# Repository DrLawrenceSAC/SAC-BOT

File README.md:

# SAC-BOT
A repository for the design and development of low-cost, open-source, beginner robotics platforms tailored to competition in RoboCup Junior events.

The design goals for these designs are as follows:
- low-cost for ease of addoption within and beyond our program
- functional, not perfect - allowing immediate engagement, and encouraing student-led modification and improvement.
- designed for specific goals of [RoboCup Junior](https://www.robocup.org/)

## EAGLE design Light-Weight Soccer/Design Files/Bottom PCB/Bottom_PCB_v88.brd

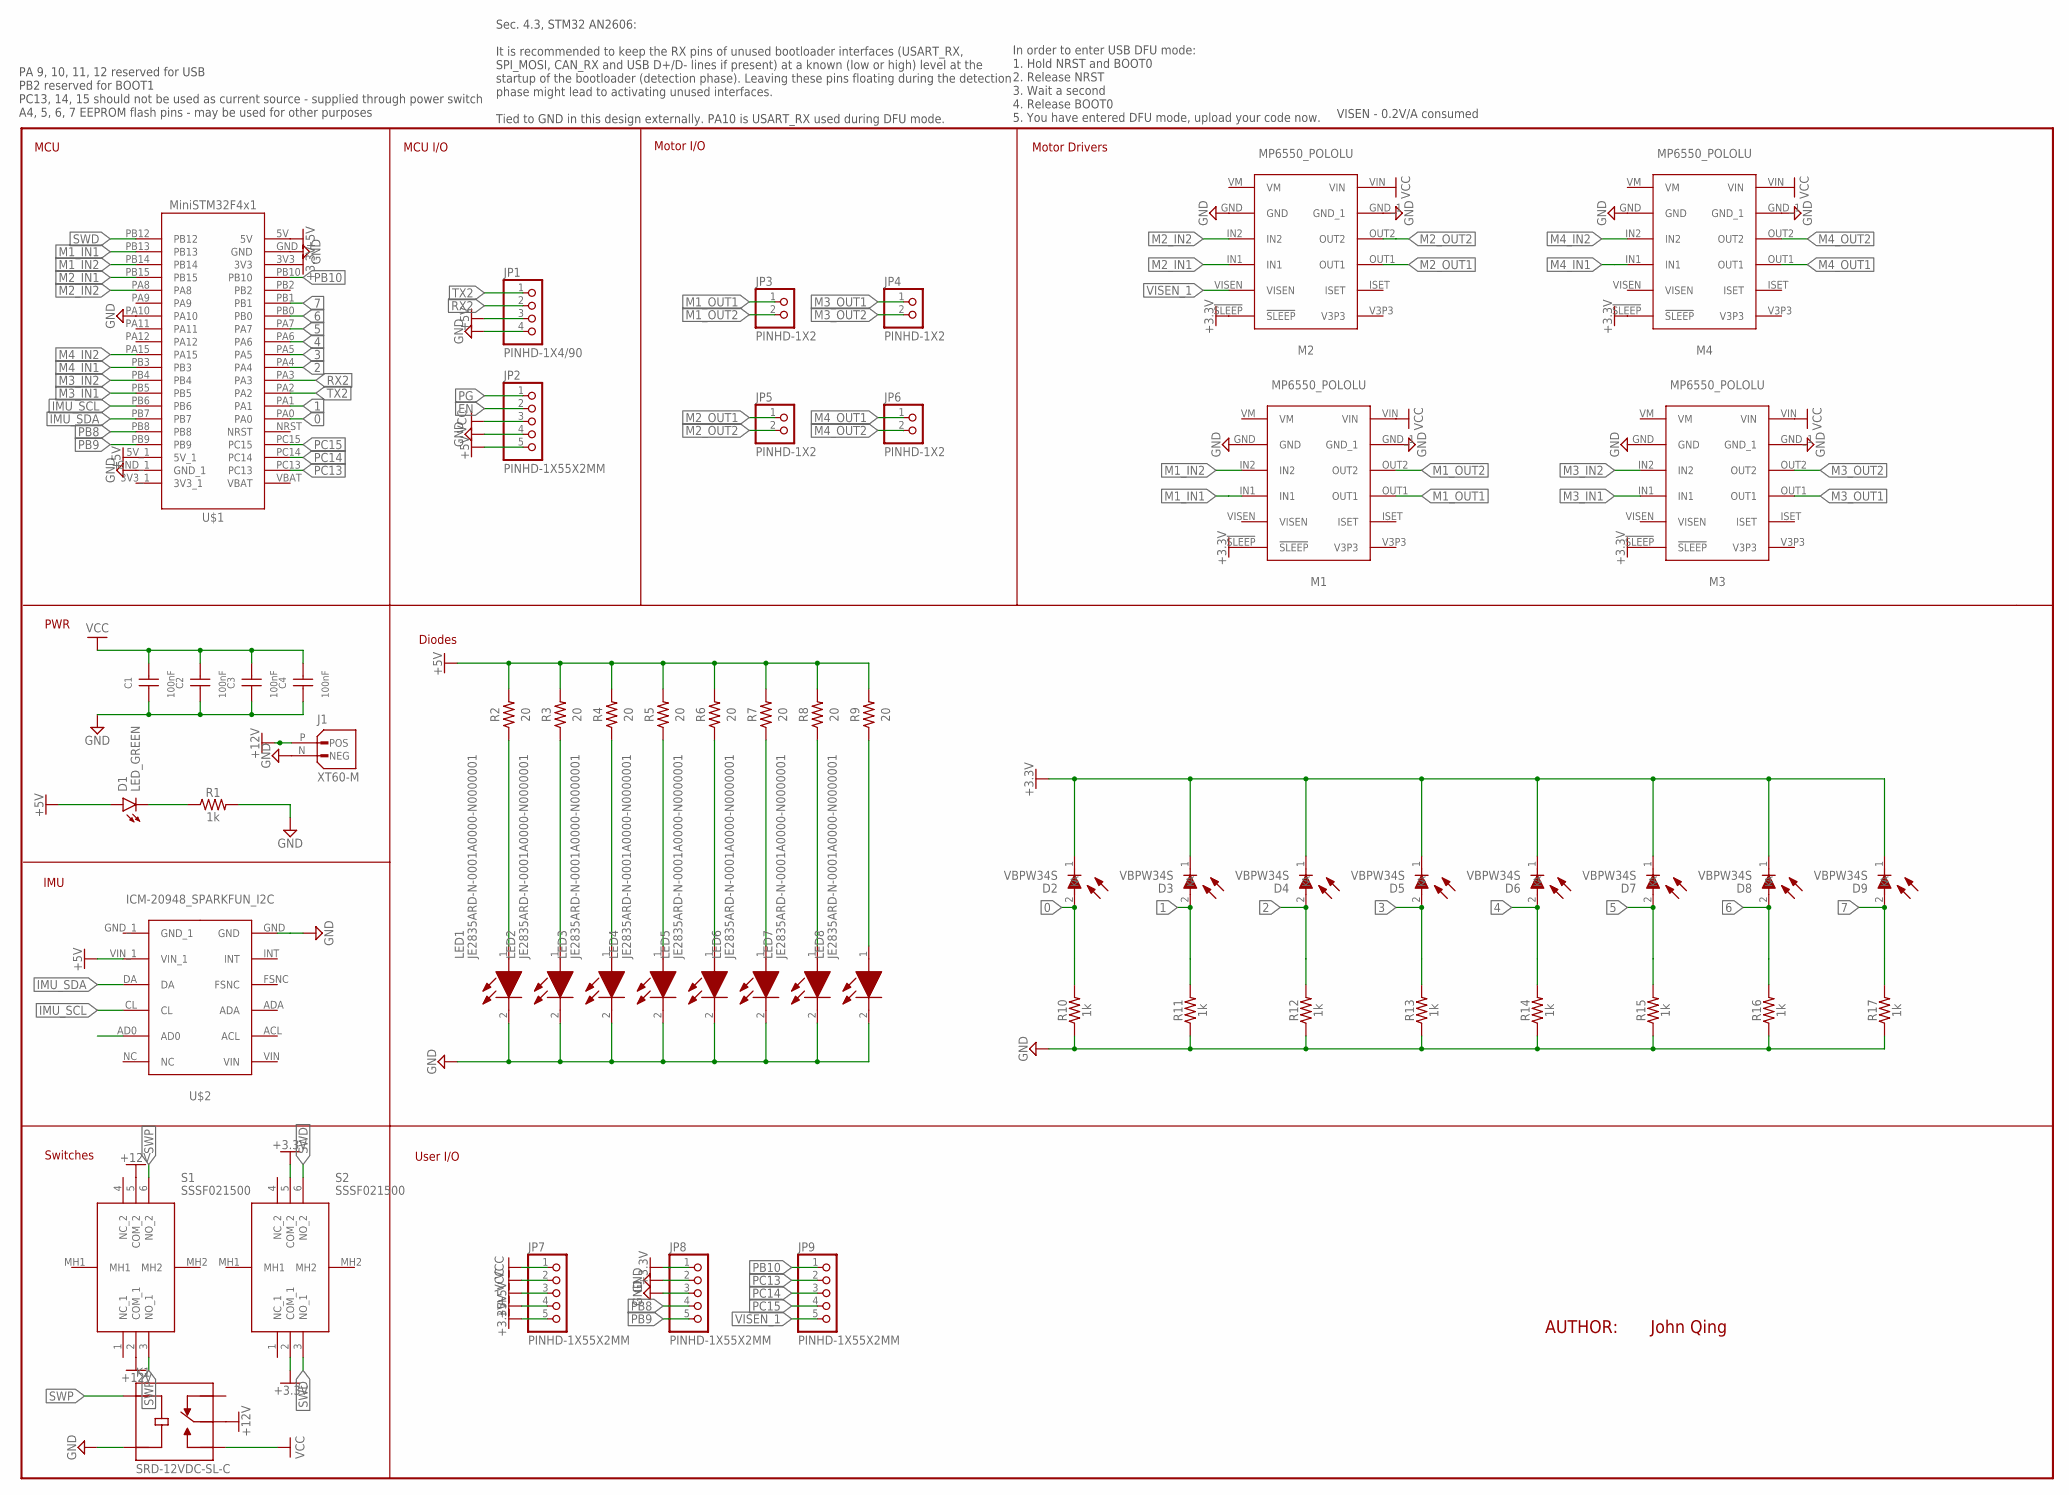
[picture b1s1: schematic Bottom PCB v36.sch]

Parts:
C1, C2, C3, C4: 100nF; WCAP-CSGP_0603_W
D1: LED_GREEN; LEDC1005X25N_FLAT-G
D2, D3, D4, D5, D6, D7, D8, D9: VBPW34S
J1: XT60-M; AMASS_XT60-M
JP1: PINHD-1X4/90; 1X04/90
JP2, JP7, JP8, JP9: PINHD-1X55X2MM; 1_05X2MM
JP3, JP4, JP5, JP6: PINHD-1X2; 1X02
K1: SRD-12VDC-SL-C; RELAY_SRD-12VDC-SL-C
LED1, LED2, LED3, LED4, LED5, LED6, LED7, LED8: JE2835ARD-N-0001A0000-N0000001; JE2835ARDN0001A0000N0000001
M1, M2, M3, M4: MP6550_POLOLU
R1, R10, R11, R12, R13, R14, R15, R16, R17: 1k; 0603
R2, R3, R4, R5, R6, R7, R8, R9: 20; RESC3224X71
S1, S2: SSSF021500
U$1: MINISTM32F4X1
U$2: ICM-20948_SPARKFUN_I2C

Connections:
0: D2.2 (A), R10.2, U$1.PA0
1: D3.2 (A), R11.2, U$1.PA1
2: D4.2 (A), R12.2, U$1.PA4
3: D5.2 (A), R13.2, U$1.PA5
4: D6.2 (A), R14.2, U$1.PA6
5: D7.2 (A), R15.2, U$1.PA7
6: D8.2 (A), R16.2, U$1.PB0
7: D9.2 (A), R17.2, U$1.PB1
+3.3V: D2.1 (K), D3.1 (K), D4.1 (K), D5.1 (K), D6.1 (K), D7.1 (K), D8.1 (K), D9.1 (K), JP7.5, JP8.1, M1.!SLEEP, M2.!SLEEP, M3.!SLEEP, M4.!SLEEP, S2.2 (COM_1), S2.5 (COM_2), U$1.3V3
+5V: D1.A, JP1.3, JP2.5, JP7.3, JP7.4, R2.2, R3.2, R4.2, R5.2, R6.2, R7.2, R8.2, R9.2, U$1.5V, U$1.5V_1, U$2.VIN_1
+12V: J1.P (POS), K1.COM, S1.2 (COM_1), S1.5 (COM_2)
EN: JP2.2
GND: C1.1, C2.1, C3.1, C4.1, J1.N (NEG), JP1.4, JP2.4, JP8.2, JP8.3, K1.COIL2, LED1.2 (K), LED2.2 (K), LED3.2 (K), LED4.2 (K), LED5.2 (K), LED6.2 (K), LED7.2 (K), LED8.2 (K), M1.GND, M1.GND_1, M2.GND, M2.GND_1, M3.GND, M3.GND_1, M4.GND, M4.GND_1, R1.2, R10.1, R11.1, R12.1, R13.1, R14.1, R15.1, R16.1, R17.1, U$1.GND, U$1.GND_1, U$1.PA10, U$2.GND
IMU_SCL: U$1.PB6, U$2.CL
IMU_SDA: U$1.PB7, U$2.DA
M1_IN1: M1.IN1, U$1.PB13
M1_IN2: M1.IN2, U$1.PB14
M1_OUT1: JP3.1, M1.OUT1
M1_OUT2: JP3.2, M1.OUT2
M2_IN1: M2.IN1, U$1.PB15
M2_IN2: M2.IN2, U$1.PA8
M2_OUT1: JP5.1, M2.OUT1
M2_OUT2: JP5.2, M2.OUT2
M3_IN1: M3.IN1, U$1.PB5
M3_IN2: M3.IN2, U$1.PB4
M3_OUT1: JP4.1, M3.OUT1
M3_OUT2: JP4.2, M3.OUT2
M4_IN1: M4.IN1, U$1.PB3
M4_IN2: M4.IN2, U$1.PA15
M4_OUT1: JP6.1, M4.OUT1
M4_OUT2: JP6.2, M4.OUT2
unnamed: D1.C, R1.1
unnamed: LED1.1 (A), R2.1
unnamed: LED2.1 (A), R3.1
unnamed: LED3.1 (A), R4.1
unnamed: LED4.1 (A), R5.1
unnamed: LED5.1 (A), R6.1
unnamed: LED6.1 (A), R7.1
unnamed: LED7.1 (A), R8.1
unnamed: LED8.1 (A), R9.1
PB8: JP8.4, U$1.PB8
PB9: JP8.5, U$1.PB9
PB10: JP9.1, U$1.PB10
PC13: JP9.2, U$1.PC13
PC14: JP9.3, U$1.PC14
PC15: JP9.4, U$1.PC15
PG: JP2.1
RX2: JP1.2, U$1.PA3
SWD: S2.3 (NO_1), S2.6 (NO_2), U$1.PB12
SWP: K1.COIL1, S1.3 (NO_1), S1.6 (NO_2)
TX2: JP1.1, U$1.PA2
VCC: C1.2, C2.2, C3.2, C4.2, JP2.3, JP7.1, JP7.2, K1.NO, M1.VIN, M2.VIN, M3.VIN, M4.VIN
VISEN_1: JP9.5, M2.VISEN

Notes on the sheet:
MCU
MCU I/O
Motor I/O
Motor Drivers
PWR
AUTHOR:
John Qing
IMU
Diodes
Switches
User I/O
PA 9, 10, 11, 12 reserved for USB PB2 reserved for BOOT1 PC13, 14, 15 should not be used as current source - supplied through power switch A4, 5, 6, 7 EEPROM flash pins - may be used for other purposes
Sec. 4.3, STM32 AN2606: It is recommended to keep the RX pins of unused bootloader interfaces (USART_RX, SPI_MOSI, CAN_RX and USB D+/D- lines if present) at a known (low or high) level at the startup of the bootloader (detection phase). Leaving these pins floating during the detection phase might l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
In order to enter USB DFU mode: 1. Hold NRST and BOOT0 2. Release NRST 3. Wait a second 4. Release BOOT0 5. You have entered DFU mode, upload your code now.
VISEN - 0.2V/A consumed

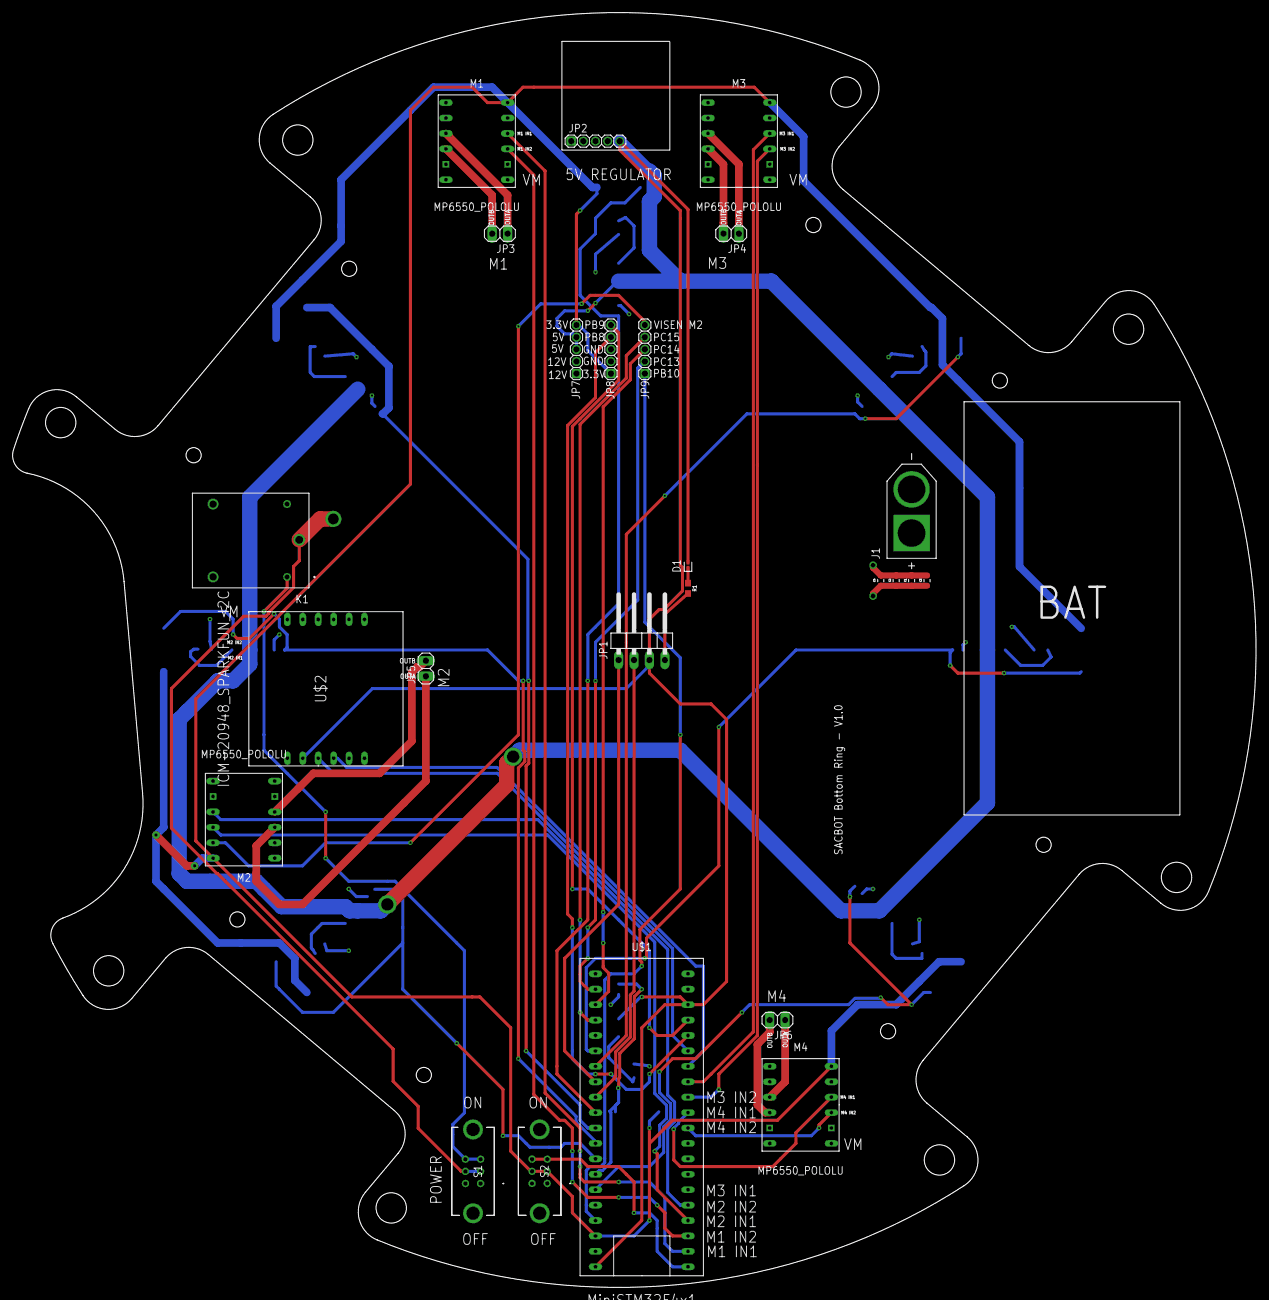
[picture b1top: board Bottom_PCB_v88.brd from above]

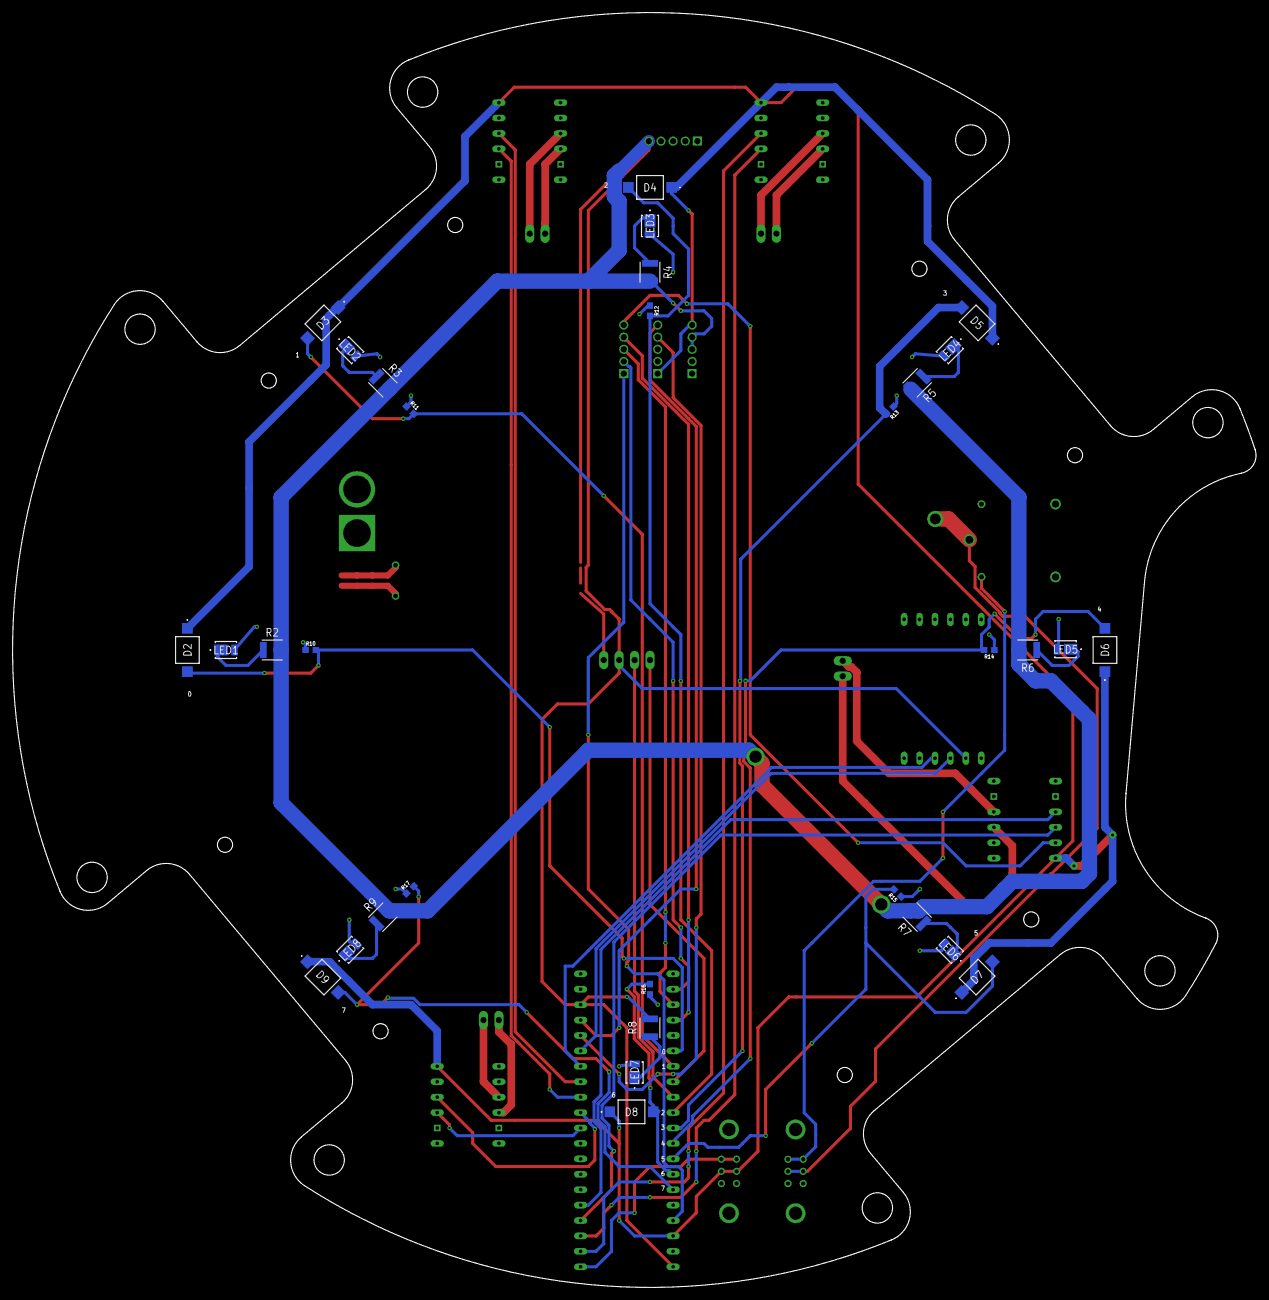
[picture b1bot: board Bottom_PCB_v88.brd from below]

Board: 4 copper layers, 204.8 x 210.0 mm, 57 parts (32 on the bottom side), 51 nets.

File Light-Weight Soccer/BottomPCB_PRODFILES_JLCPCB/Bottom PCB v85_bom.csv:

Comment,Designator,Footprint,LCSC Part #
1k,R1 R10 R11 R12 R13 R14 R15 R16 R17,0603,
20,R2 R3 R4 R5 R6 R7 R8 R9,RESC3224X71,
100nF,C1 C2 C3 C4,WCAP-CSGP_0603_W,
ICM-20948_SPARKFUN_I2C,U$2,ICM-20948_SPARKFUN_I2C,
JE2835ARD-N-0001A0000-N0000001,LED1 LED2 LED3 LED4 LED5 LED6 LED7 LED8,JE2835ARDN0001A0000N0000001,
LED_GREEN,D1,LEDC1005X25N_FLAT-G,
MINISTM32F4X1,U$1,MINISTM32F4X1,
MP6550_POLOLU,M1 M2 M3 M4,MP6550_POLOLU,
PINHD-1X2,JP3 JP4 JP5 JP6,1X02,
PINHD-1X4/90,JP1,1X04/90,
PINHD-1X55X2MM,JP2 JP7 JP8 JP9,1_05X2MM,
SRD-12VDC-SL-C,K1,RELAY_SRD-12VDC-SL-C,
SSSF021500,S1 S2,SSSF021500,
VBPW34S,D2 D3 D4 D5 D6 D7 D8 D9,VBPW34S,
XT60-M,J1,AMASS_XT60-M,

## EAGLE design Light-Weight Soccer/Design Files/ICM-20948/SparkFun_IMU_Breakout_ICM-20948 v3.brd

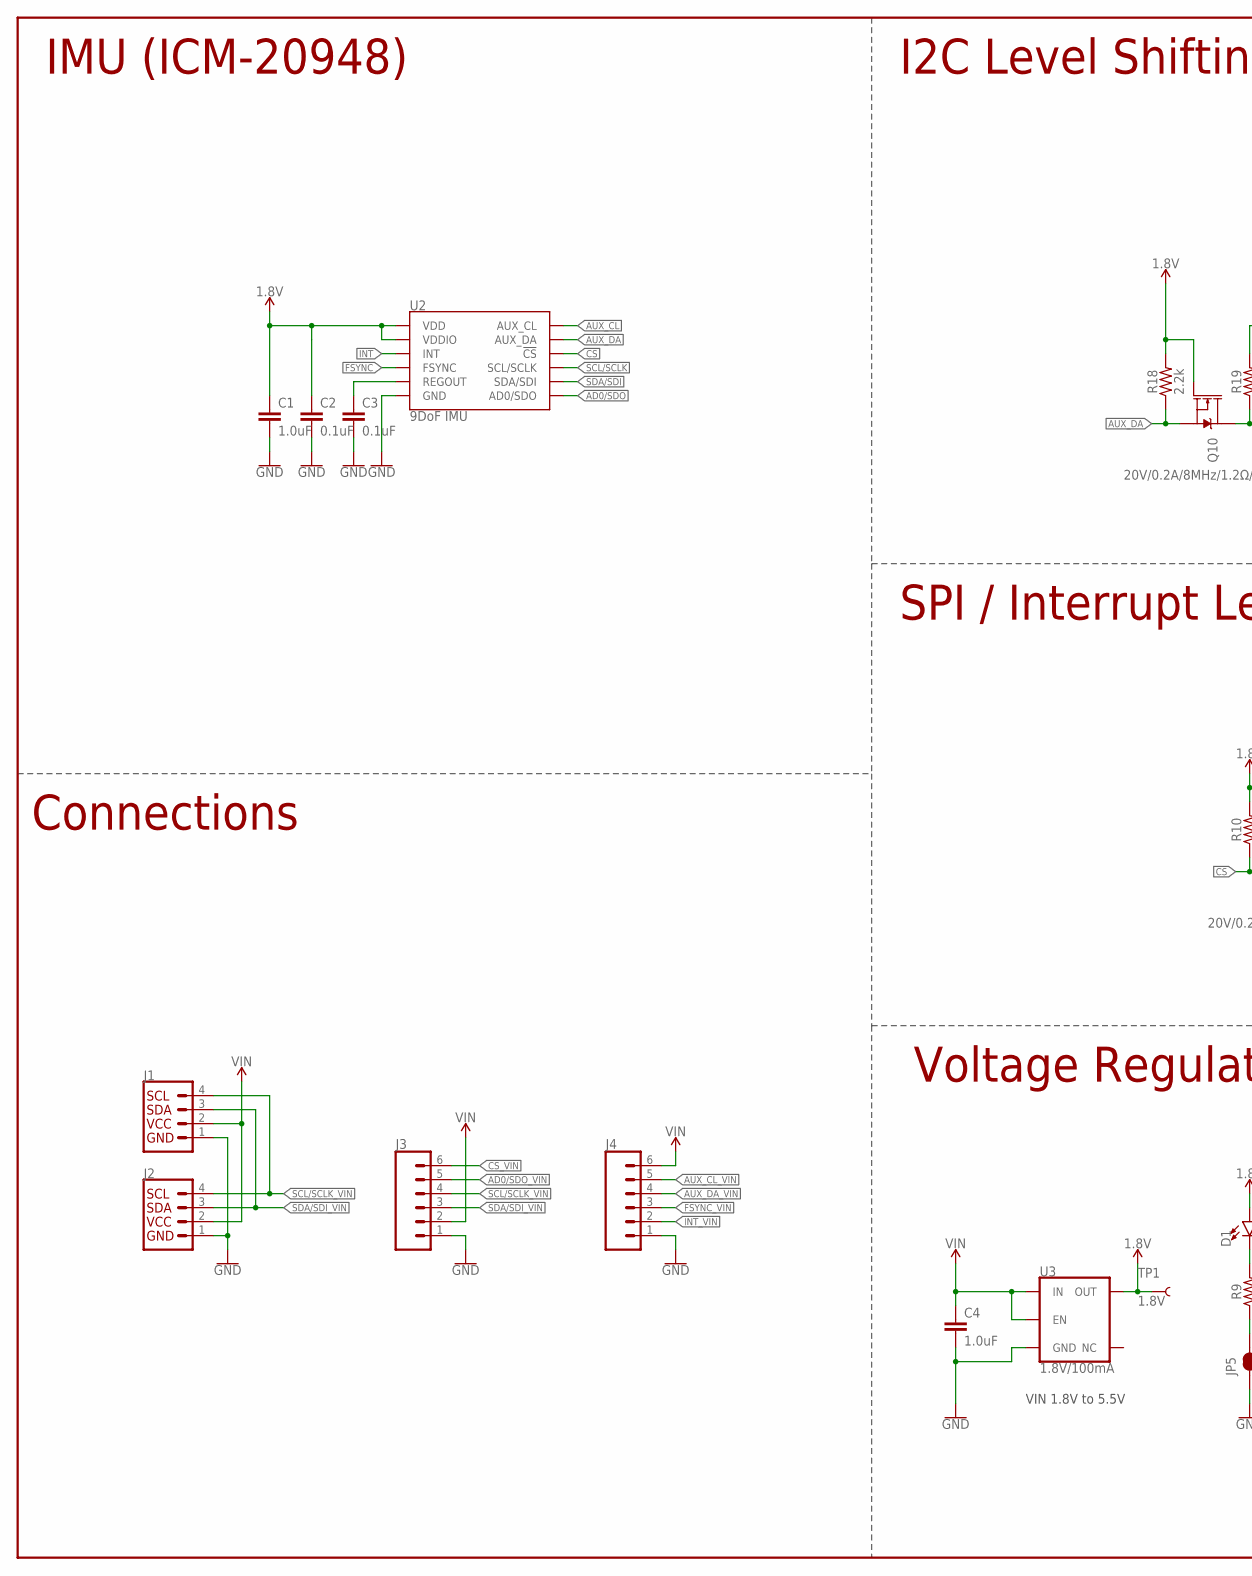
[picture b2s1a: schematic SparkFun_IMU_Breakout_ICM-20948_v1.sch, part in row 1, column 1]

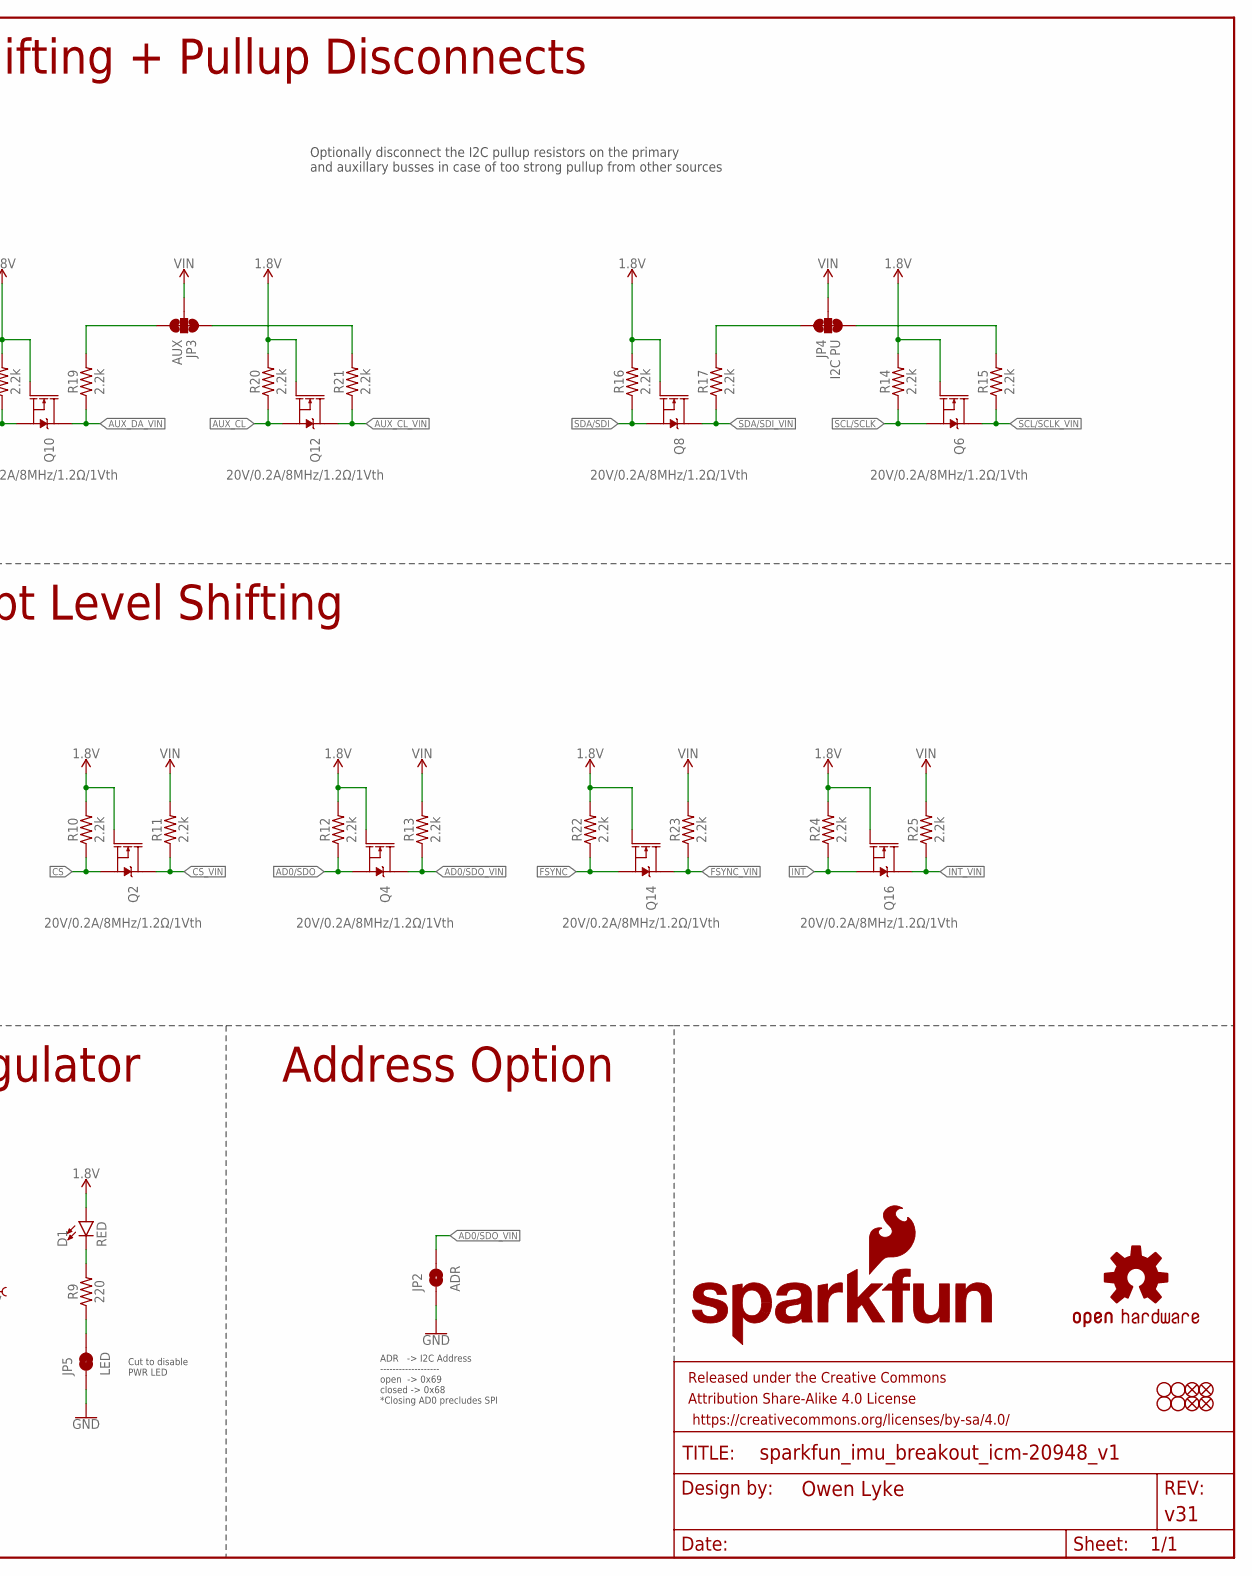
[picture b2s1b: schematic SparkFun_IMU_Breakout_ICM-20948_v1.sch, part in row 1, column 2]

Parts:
C1, C4: 1.0uF; 0603
C2, C3: 0.1uF; 0603
D1: RED; LED-0603
FD1, FD2, FD3, FD4: FIDUCIAL1X2; FIDUCIAL-1X2
FRAME2: FRAME-LEDGER; CREATIVE_COMMONS
H1, H2, H3, H4: STAND-OFF
J1, J2: QWIIC_CONNECTORJS-1MM; JST04_1MM_RA
J3, J4: CONN_06NO_SILK_NO_POP; 1X06_NO_SILK
JP2: ADR; SMT-JUMPER_2_NO_SILK
JP3: AUX; SMT-JUMPER_3_2-NC_TRACE_SILK
JP4: I2C PU; SMT-JUMPER_3_2-NC_TRACE_SILK
JP5: LED; SMT-JUMPER_2_NC_TRACE_SILK
LOGO1: SFE_LOGO_NAME_FLAME.1_INCH; SFE_LOGO_NAME_FLAME_.1
LOGO2: OSHW-LOGOMINI; OSHW-LOGO-MINI
Q2, Q4, Q6, Q8, Q10, Q12, Q14, Q16: 20V/0.2A/8MHz/1.2Ω/1Vth; SOT-416FL
R9: 220; 0603
R10, R11, R12, R13, R14, R15, R16, R17, R18, R19, R20, R21, R22, R23, R24, R25: 2.2k; 0402-TIGHT
TP1: 1.8V; PAD.03X.03
U2: 9DoF IMU; QFN24-3X3
U3: 1.8V/100mA; SC70

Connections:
1.8V: C1.1, C2.1, D1.A, Q2.1 (G), Q4.1 (G), Q6.1 (G), Q8.1 (G), Q10.1 (G), Q12.1 (G), Q14.1 (G), Q16.1 (G), R10.2, R12.2, R14.2, R16.2, R18.2, R20.2, R22.2, R24.2, TP1.P$1, U2.8 (VDDIO), U2.13 (VDD), U3.5 (OUT)
!CS: Q2.2 (S), R10.1, U2.22 (!CS)
!CS!_VIN: J3.6, Q2.3 (D), R11.1
AD0/SDO: Q4.2 (S), R12.1, U2.9 (AD0/SDO)
AD0/SDO_VIN: J3.5, JP2.2, Q4.3 (D), R13.1
AUX_CL: Q12.2 (S), R20.1, U2.7 (AUX_CL)
AUX_CL_VIN: J4.5, Q12.3 (D), R21.1
AUX_DA: Q10.2 (S), R18.1, U2.21 (AUX_DA)
AUX_DA_VIN: J4.4, Q10.3 (D), R19.1
FSYNC: Q14.2 (S), R22.1, U2.11 (FSYNC)
FSYNC_VIN: J4.3, Q14.3 (D), R23.1
GND: C1.2, C2.2, C3.2, C4.2, J1.1, J2.1, J3.1, J4.1, JP2.1, JP5.1, U2.18 (GND), U2.20 (GND), U3.2 (GND)
INT: Q16.2 (S), R24.1, U2.12 (INT)
INT_VIN: J4.2, Q16.3 (D), R25.1
unnamed: C3.1, U2.10 (REGOUT)
unnamed: JP4.3, R15.2
unnamed: JP4.1, R17.2
unnamed: JP3.1, R21.2
unnamed: JP3.3, R19.2
unnamed: D1.C, R9.2
unnamed: JP5.2, R9.1
SCL/SCLK: Q6.2 (S), R14.1, U2.23 (SCL/SCLK)
SCL/SCLK_VIN: J1.4, J2.4, J3.4, Q6.3 (D), R15.1
SDA/SDI: Q8.2 (S), R16.1, U2.24 (SDA/SDI)
SDA/SDI_VIN: J1.3, J2.3, J3.3, Q8.3 (D), R17.1
VIN: C4.1, J1.2, J2.2, J3.2, J4.6, JP3.2, JP4.2, R11.2, R13.2, R23.2, R25.2, U3.1 (IN), U3.3 (EN)

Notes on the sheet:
VIN 1.8V to 5.5V
IMU (ICM-20948)
I2C Level Shifting + Pullup Disconnects
Connections
Voltage Regulator
SPI / Interrupt Level Shifting
ADR -> I2C Address ------------------- open -> 0x69 closed -> 0x68 *Closing AD0 precludes SPI
Optionally disconnect the I2C pullup resistors on the primary and auxillary busses in case of too strong pullup from other sources
Cut to disable PWR LED
Address Option

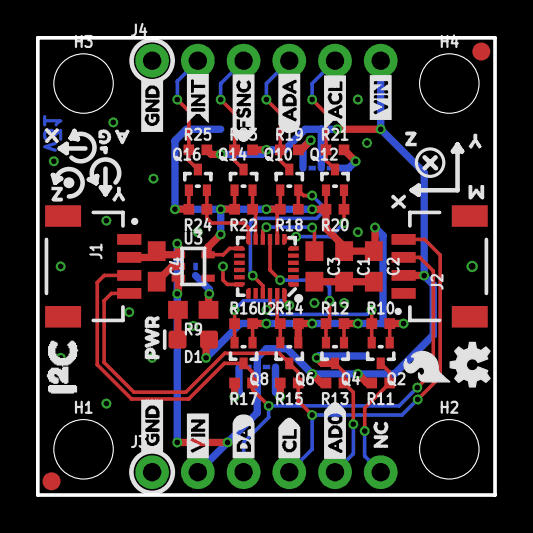
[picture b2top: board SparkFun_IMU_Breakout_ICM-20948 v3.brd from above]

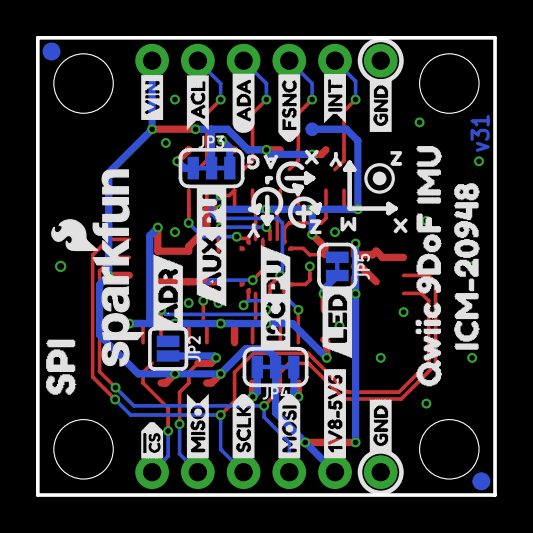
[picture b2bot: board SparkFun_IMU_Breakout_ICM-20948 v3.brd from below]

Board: 2 copper layers, 25.4 x 25.4 mm, 104 parts (36 on the bottom side), 26 nets.

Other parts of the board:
U$1, U$2, U$22, U$24: GND4
U$3: PWR0
U$4, U$21: INT3
U$5, U$20: FSNC2
U$6, U$19: ACL1
U$7, U$18: ADA0
U$8: MISO13
U$9: MOSI14
U$10: SCLK15
U$11: #CS16
U$12: 1V8#5V57
U$13, U$30, U$44: VIN5
U$14: NC17
U$15: CL4
U$16: DA2
U$17: AD012
U$23: ADR2
U$25: I2C_PU21
U$26: SPI19
U$27: AUX_PU24
U$28: SFE_LOGO_FLAME_.1
U$29: LED23
U$31: ICM#2094820
U$34, U$40, U$50, U$57: X0
U$35, U$41, U$51, U$58: Y1
U$36, U$42, U$52, U$59: Z2
U$37, U$60: G5
U$38, U$61: A4
U$39, U$49: M3
U$43: QWIIC_9DOF_IMU_0
U$45: I#C1

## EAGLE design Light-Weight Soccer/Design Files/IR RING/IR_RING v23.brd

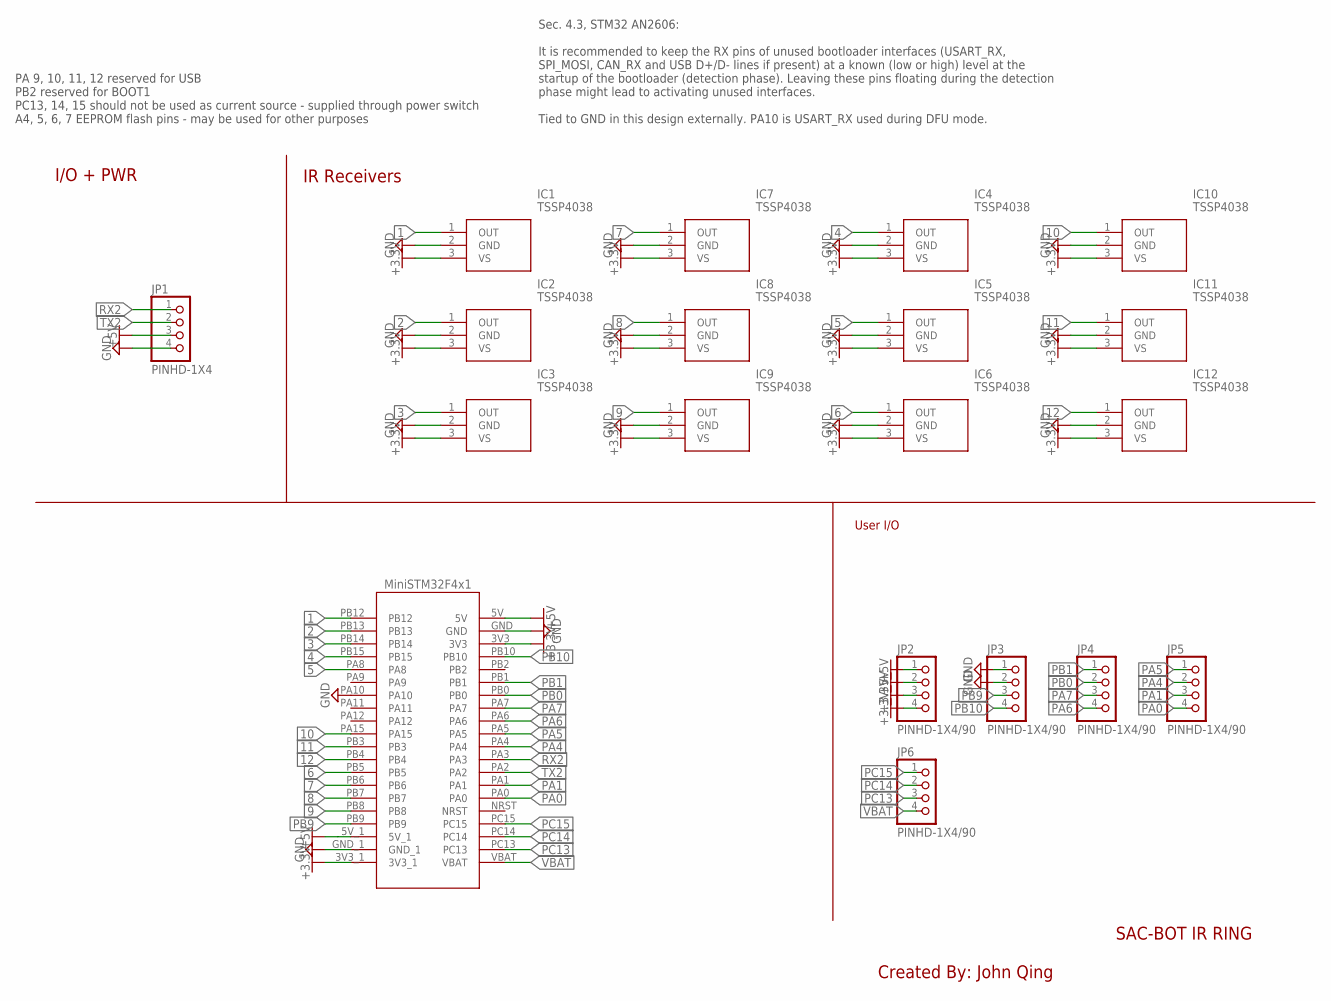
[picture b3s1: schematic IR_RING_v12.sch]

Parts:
IC1, IC2, IC3, IC4, IC5, IC6, IC7, IC8, IC9, IC10, IC11, IC12: TSSP4038
JP1: PINHD-1X4; 1X04
JP2, JP3, JP4, JP5, JP6: PINHD-1X4/90; 1X04/90
U$1: MINISTM32F4X1

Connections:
1: IC1.1 (OUT), U$1.PB12
2: IC2.1 (OUT), U$1.PB13
3: IC3.1 (OUT), U$1.PB14
4: IC4.1 (OUT), U$1.PB15
5: IC5.1 (OUT), U$1.PA8
6: IC6.1 (OUT), U$1.PB5
7: IC7.1 (OUT), U$1.PB6
8: IC8.1 (OUT), U$1.PB7
9: IC9.1 (OUT), U$1.PB8
10: IC10.1 (OUT), U$1.PA15
11: IC11.1 (OUT), U$1.PB3
12: IC12.1 (OUT), U$1.PB4
+3.3V: IC1.3 (VS), IC2.3 (VS), IC3.3 (VS), IC4.3 (VS), IC5.3 (VS), IC6.3 (VS), IC7.3 (VS), IC8.3 (VS), IC9.3 (VS), IC10.3 (VS), IC11.3 (VS), IC12.3 (VS), JP2.3, JP2.4, U$1.3V3, U$1.3V3_1
+5V: JP1.3, JP2.1, JP2.2, U$1.5V, U$1.5V_1
GND: IC1.2 (GND), IC2.2 (GND), IC3.2 (GND), IC4.2 (GND), IC5.2 (GND), IC6.2 (GND), IC7.2 (GND), IC8.2 (GND), IC9.2 (GND), IC10.2 (GND), IC11.2 (GND), IC12.2 (GND), JP1.4, JP3.1, JP3.2, U$1.GND, U$1.PA10
GND_1: U$1.GND_1
PA0: JP5.4, U$1.PA0
PA1: JP5.3, U$1.PA1
PA4: JP5.2, U$1.PA4
PA5: JP5.1, U$1.PA5
PA6: JP4.4, U$1.PA6
PA7: JP4.3, U$1.PA7
PB0: JP4.2, U$1.PB0
PB1: JP4.1, U$1.PB1
PB9: JP3.3, U$1.PB9
PB10: JP3.4, U$1.PB10
PC13: JP6.3, U$1.PC13
PC14: JP6.2, U$1.PC14
PC15: JP6.1, U$1.PC15
RX2: JP1.1, U$1.PA3
TX2: JP1.2, U$1.PA2
VBAT: JP6.4, U$1.VBAT

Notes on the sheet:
Created By: John Qing
SAC-BOT IR RING
IR Receivers
I/O + PWR
PA 9, 10, 11, 12 reserved for USB PB2 reserved for BOOT1 PC13, 14, 15 should not be used as current source - supplied through power switch A4, 5, 6, 7 EEPROM flash pins - may be used for other purposes
Sec. 4.3, STM32 AN2606: It is recommended to keep the RX pins of unused bootloader interfaces (USART_RX, SPI_MOSI, CAN_RX and USB D+/D- lines if present) at a known (low or high) level at the startup of the bootloader (detection phase). Leaving these pins floating during the detection phase might l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
User I/O

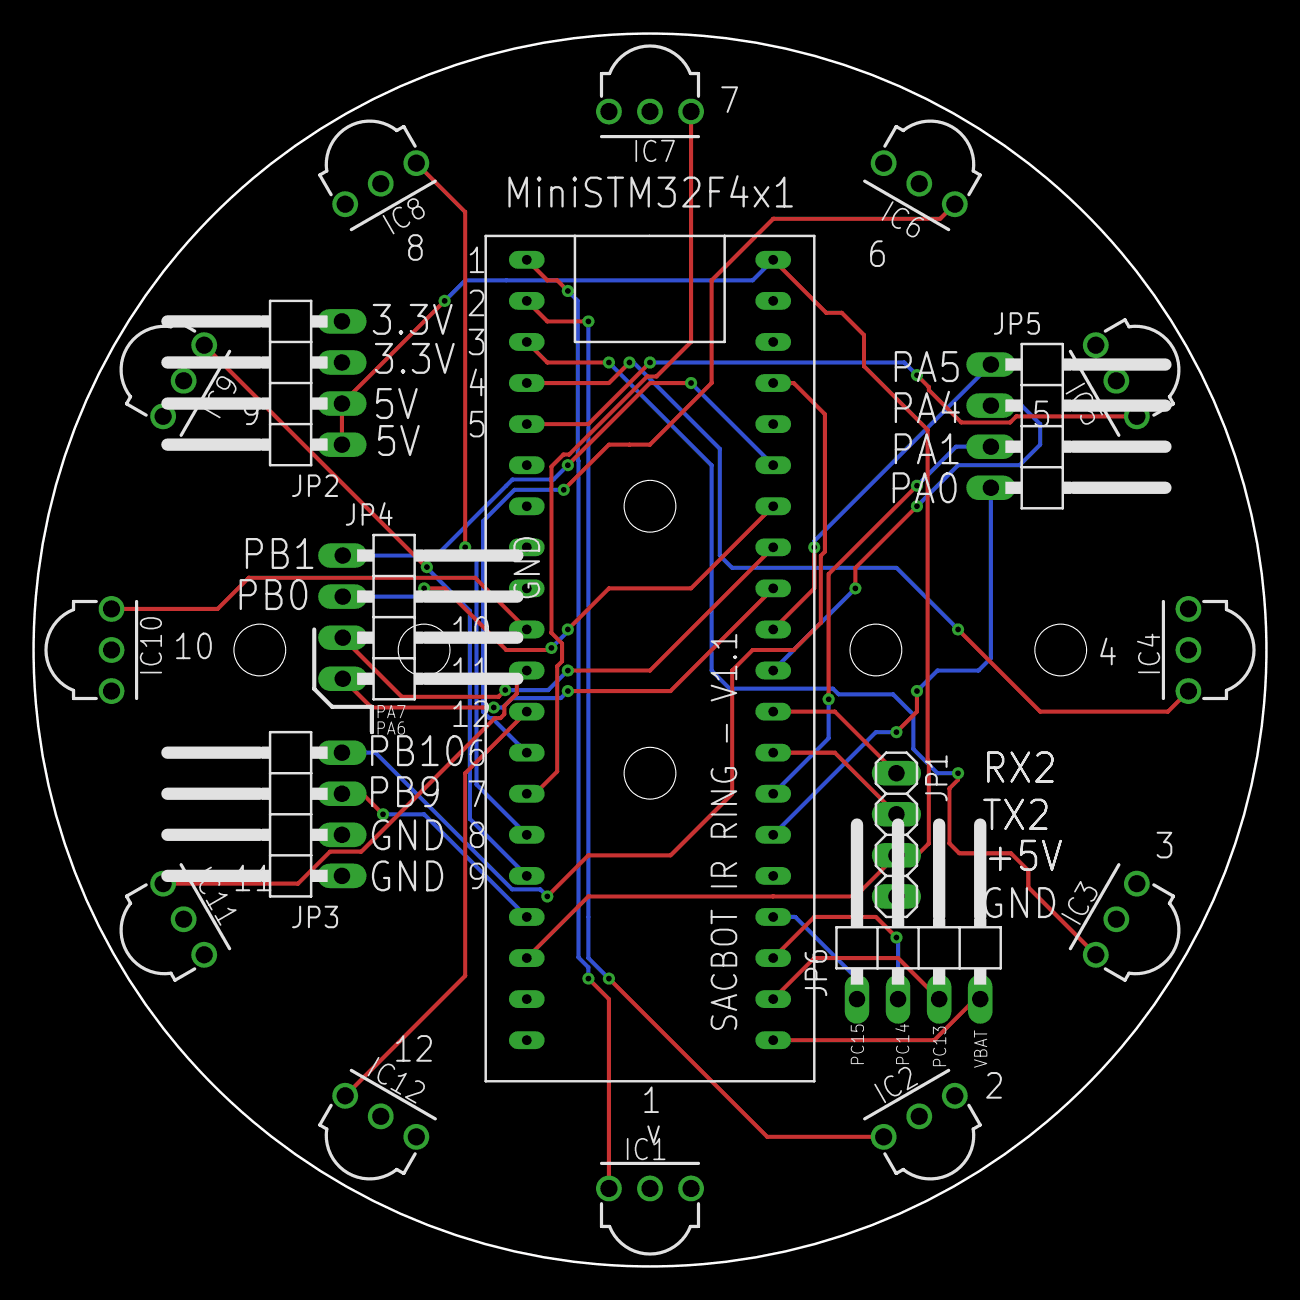
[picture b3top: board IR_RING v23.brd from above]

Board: 4 copper layers, 76.2 x 76.2 mm, 19 parts (0 on the bottom side), 31 nets.

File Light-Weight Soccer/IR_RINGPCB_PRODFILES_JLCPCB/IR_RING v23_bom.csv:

Comment,Designator,Footprint,LCSC Part #
MINISTM32F4X1,U$1,MINISTM32F4X1,
PINHD-1X4,JP1,1X04,
PINHD-1X4/90,JP2 JP3 JP4 JP5 JP6,1X04/90,
TSSP4038,IC1 IC2 IC3 IC4 IC5 IC6 IC7 IC8 IC9 IC10 IC11 IC12,TSSP4038,

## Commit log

2024-07-23 Adding folder for LWS
2024-07-23 Adding directory for RL
2024-07-24 fix comma issue
2024-09-28 final update
2024-09-28 Add design files
2024-09-28 Added all design files
2025-06-20 Rename RescueLine/designFiles/2425-SACBOT-LINE Drawing-V6 v1.pdf to RescueLine/designFiles/oldVersions/2425-SACBOT-LINE Drawing-V6 v1.pdf
2025-06-20 Rename RescueLine/designFiles/2425-SACBOT-LINEv6.f3d to RescueLine/designFiles/oldVersions/2425-SACBOT-LINEv6.f3d
2025-06-20 Rename RescueLine/designFiles/2425-SACBOT-LineV1.ai to RescueLine/designFiles/oldVersions/2425-SACBOT-LineV1.ai
2025-06-20 Adding v7.4 files
2025-10-15 adding 2526 version of SACbot test
2025-10-27 fixing reversed motor/IR sensors

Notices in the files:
parts and their libraries:
SparkFun-Resistors: Licensing: Creative Commons ShareAlike 4.0 International - https://creativecommons.org/licenses/by-sa/4.0
Wurth_Capacitors_WCAP-CSGP: Copyright: Würth Elektronik
SparkFun-Aesthetics: Released under the Creative Commons Attribution Share-Alike 4.0 License
